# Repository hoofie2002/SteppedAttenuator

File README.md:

This project provides a schematic and PCB for a stepped attenuator

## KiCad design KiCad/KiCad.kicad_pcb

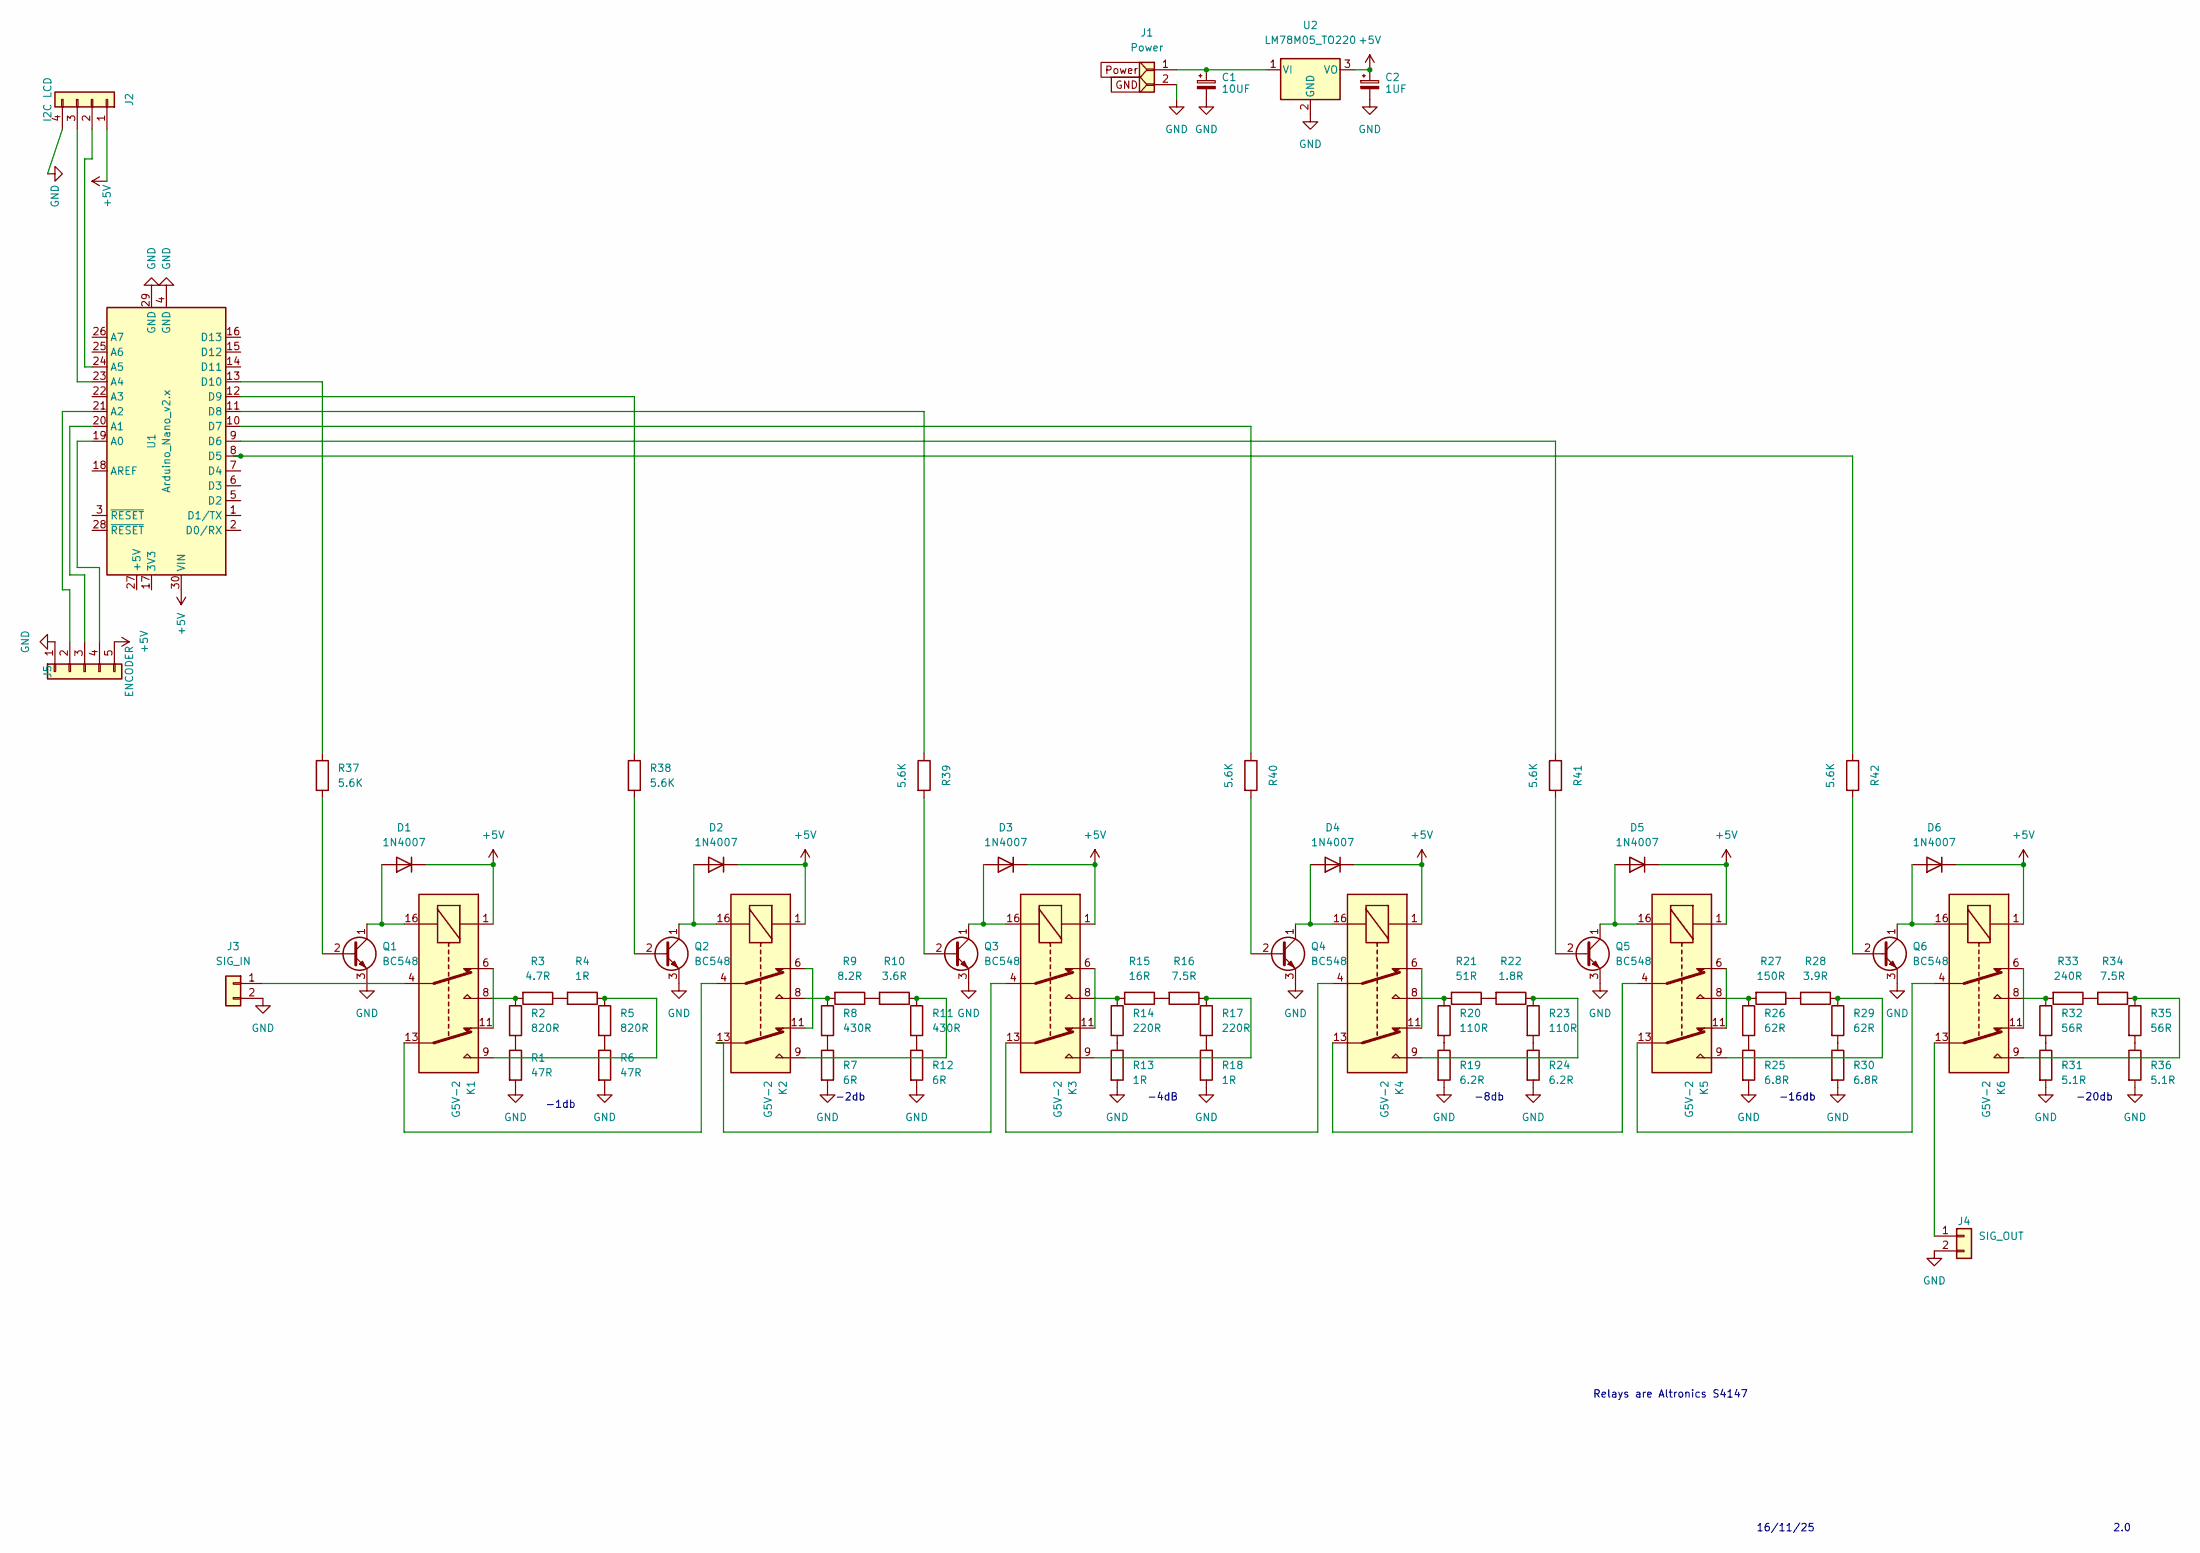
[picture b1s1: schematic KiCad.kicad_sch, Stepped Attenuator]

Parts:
C1: 10UF; CP_Radial_D4.0mm_P2.00mm
C2: 1UF; CP_Radial_D4.0mm_P2.00mm
D1, D2, D3, D4, D5, D6: 1N4007; D_DO-41_SOD81_P10.16mm_Horizontal
J1: Power; BarrelJack_Horizontal
J2: I2C LCD; PinHeader_1x04_P2.54mm_Vertical
J3: SIG_IN; SMA_Amphenol_901-143_Horizontal
J4: SIG_OUT; SMA_Amphenol_901-143_Horizontal
J5: ENCODER; PinHeader_1x05_P2.54mm_Vertical
K1, K2, K3, K4, K5, K6: G5V-2; Relay_DPDT_Omron_G5V-2
Q1, Q2, Q3, Q4, Q5, Q6: BC548; TO-92_Inline
R1, R6: 47R; R_Axial_DIN0207_L6.3mm_D2.5mm_P7.62mm_Horizontal
R2, R5: 820R; R_Axial_DIN0207_L6.3mm_D2.5mm_P7.62mm_Horizontal
R3: 4.7R; R_Axial_DIN0207_L6.3mm_D2.5mm_P7.62mm_Horizontal
R4, R13, R18: 1R; R_Axial_DIN0207_L6.3mm_D2.5mm_P7.62mm_Horizontal
R7, R12: 6R; R_Axial_DIN0207_L6.3mm_D2.5mm_P7.62mm_Horizontal
R8, R11: 430R; R_Axial_DIN0207_L6.3mm_D2.5mm_P7.62mm_Horizontal
R9: 8.2R; R_Axial_DIN0207_L6.3mm_D2.5mm_P7.62mm_Horizontal
R10: 3.6R; R_Axial_DIN0207_L6.3mm_D2.5mm_P7.62mm_Horizontal
R14, R17: 220R; R_Axial_DIN0207_L6.3mm_D2.5mm_P7.62mm_Horizontal
R15: 16R; R_Axial_DIN0207_L6.3mm_D2.5mm_P7.62mm_Horizontal
R16, R34: 7.5R; R_Axial_DIN0207_L6.3mm_D2.5mm_P7.62mm_Horizontal
R19, R24: 6.2R; R_Axial_DIN0207_L6.3mm_D2.5mm_P7.62mm_Horizontal
R20, R23: 110R; R_Axial_DIN0207_L6.3mm_D2.5mm_P7.62mm_Horizontal
R21: 51R; R_Axial_DIN0207_L6.3mm_D2.5mm_P7.62mm_Horizontal
R22: 1.8R; R_Axial_DIN0207_L6.3mm_D2.5mm_P7.62mm_Horizontal
R25, R30: 6.8R; R_Axial_DIN0207_L6.3mm_D2.5mm_P7.62mm_Horizontal
R26, R29: 62R; R_Axial_DIN0207_L6.3mm_D2.5mm_P7.62mm_Horizontal
R27: 150R; R_Axial_DIN0207_L6.3mm_D2.5mm_P7.62mm_Horizontal
R28: 3.9R; R_Axial_DIN0207_L6.3mm_D2.5mm_P7.62mm_Horizontal
R31, R36: 5.1R; R_Axial_DIN0207_L6.3mm_D2.5mm_P7.62mm_Horizontal
R32, R35: 56R; R_Axial_DIN0207_L6.3mm_D2.5mm_P7.62mm_Horizontal
R33: 240R; R_Axial_DIN0207_L6.3mm_D2.5mm_P7.62mm_Horizontal
R37, R38, R39, R40, R41, R42: 5.6K; R_Axial_DIN0207_L6.3mm_D2.5mm_P7.62mm_Horizontal
U1: Arduino_Nano_v2.x; Arduino_Nano
U2: LM78M05_TO220; TO-220-3_Vertical

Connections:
+5V: C2.1, D1.1 (K), D2.1 (K), D3.1 (K), D4.1 (K), D5.1 (K), D6.1 (K), J2.1, J5.5, K1.1, K2.1, K3.1, K4.1, K5.1, K6.1, U1.30 (VIN), U2.3 (VO)
unnamed: C1.1, J1.1, U2.1 (VI)
unnamed: D1.2 (A), K1.16, Q1.1 (C)
unnamed: D2.2 (A), K2.16, Q2.1 (C)
unnamed: D3.2 (A), K3.16, Q3.1 (C)
unnamed: D4.2 (A), K4.16, Q4.1 (C)
unnamed: D5.2 (A), K5.16, Q5.1 (C)
unnamed: D6.2 (A), K6.16, Q6.1 (C)
unnamed: J2.2, U1.24 (A5)
unnamed: J2.3, U1.23 (A4)
unnamed: J4.1, K6.13
unnamed: J5.2, U1.21 (A2)
unnamed: J5.3, U1.20 (A1)
unnamed: J5.4, U1.19 (A0)
unnamed: K1.8, R2.1, R3.2
unnamed: K1.9, R4.1, R5.1
unnamed: K1.6, K1.11
unnamed: K1.13, K2.4
unnamed: K2.8, R8.1, R9.2
unnamed: K2.9, R10.1, R11.1
unnamed: K2.6, K2.11
unnamed: K2.13, K3.4
unnamed: K3.8, R14.1, R15.2
unnamed: K3.9, R16.1, R17.1
unnamed: K3.6, K3.11
unnamed: K3.13, K4.4
unnamed: K4.8, R20.1, R21.2
unnamed: K4.9, R22.1, R23.1
unnamed: K4.6, K4.11
unnamed: K4.13, K5.4
unnamed: K5.8, R26.1, R27.2
unnamed: K5.9, R28.1, R29.1
unnamed: K5.6, K5.11
unnamed: K5.13, K6.4
unnamed: K6.8, R32.1, R33.2
unnamed: K6.9, R34.1, R35.1
unnamed: K6.6, K6.11
unnamed: Q1.2 (B), R37.2
unnamed: Q2.2 (B), R38.2
unnamed: Q3.2 (B), R39.2
unnamed: Q4.2 (B), R40.2
unnamed: Q5.2 (B), R41.2
unnamed: Q6.2 (B), R42.2
unnamed: R1.1, R2.2
unnamed: R3.1, R4.2
unnamed: R5.2, R6.1
unnamed: R7.1, R8.2
unnamed: R9.1, R10.2
unnamed: R11.2, R12.1
unnamed: R13.1, R14.2
unnamed: R15.1, R16.2
unnamed: R17.2, R18.1
unnamed: R19.1, R20.2
unnamed: R21.1, R22.2
unnamed: R23.2, R24.1
unnamed: R25.1, R26.2
unnamed: R27.1, R28.2
unnamed: R29.2, R30.1
unnamed: R31.1, R32.2
unnamed: R33.1, R34.2
unnamed: R35.2, R36.1
unnamed: R37.1, U1.13 (D10)
unnamed: R38.1, U1.12 (D9)
unnamed: R39.1, U1.11 (D8)
unnamed: R40.1, U1.10 (D7)
unnamed: R41.1, U1.9 (D6)
unnamed: R42.1, U1.8 (D5)

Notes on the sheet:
2.0
-1db
Relays are Altronics S4147
-4dB
-8db
-16db
16/11/25
-20db
-2db

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
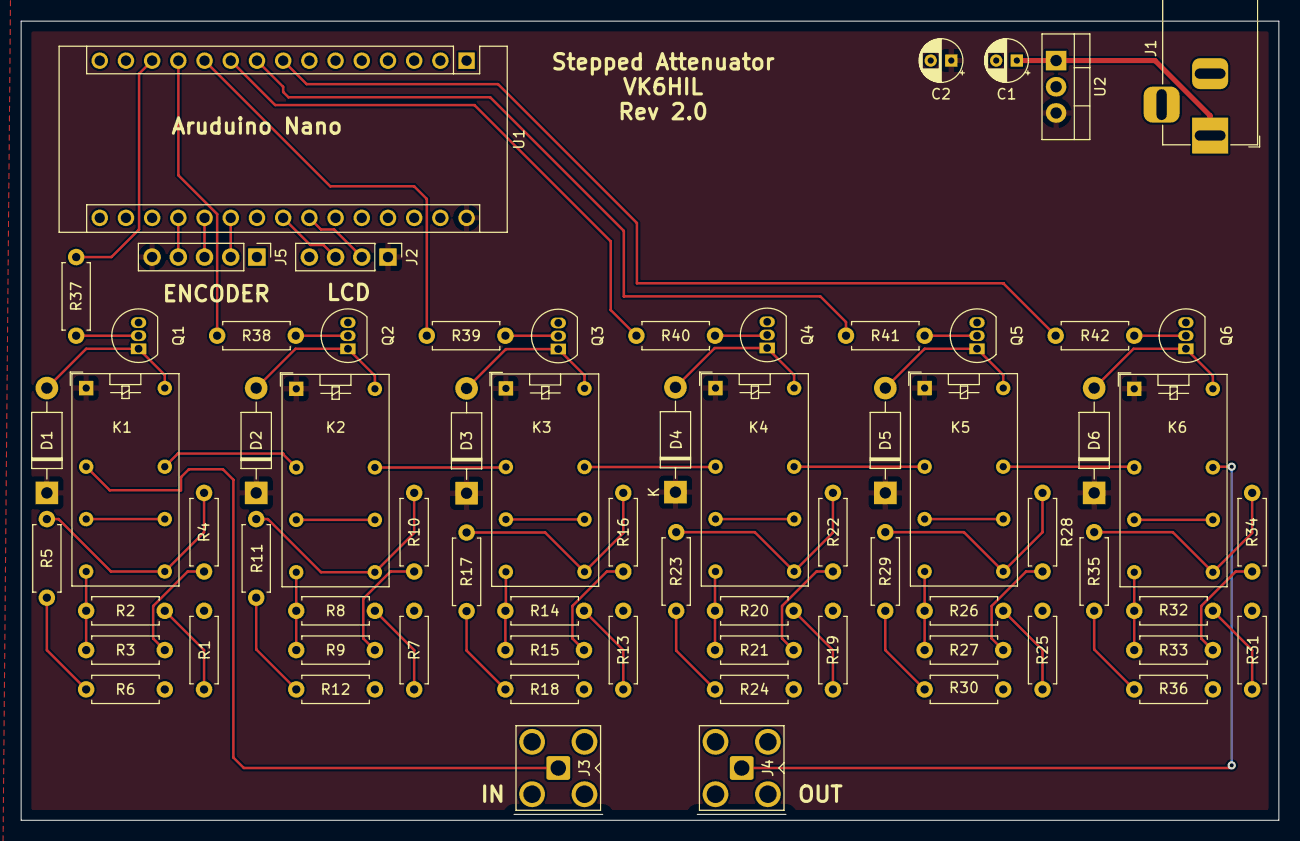
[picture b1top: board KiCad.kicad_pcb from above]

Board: 2 copper layers, 121.9 x 77.5 mm, 69 parts (0 on the bottom side), 69 nets.

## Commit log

2026-06-24 Added slowness to encoder movement
